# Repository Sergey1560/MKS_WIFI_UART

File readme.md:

# Модуль для подключения к UART плат Robin Nano

Данный модуль предназначен для использования с платами MKS Robin Nano. Вставляется вместо MKS WIFI модуля и позволяет подключиться по UART. На модуле установлен изолятор ISO 7712 и USB-UART преобразователь FT230. На разъем J3 выведены сигналы USB, на разъем J4 выведены сигналы UART.

Проект сделан в KiCad.

## Схема платы

## Архив с gerber файлами

[mks_wifi.zip](./gerber/mks_wifi.zip)

## Список компонентов

Список компонентов - [mks_wifi_bom.ods](./bom/mks_wifi_bom.ods)

| N  | Кол-во | Номинал | Размер | Link
| -----------| ---------- |---------|------- |----- |
| C1, C2     | 2          | 47pF    | 0805   | [LCSC](https://lcsc.com/product-detail/Multilayer-Ceramic-Capacitors-MLCC-SMD-SMT_YAGEO-CC0805JRNPO9BN470_C107118.html) [TERRA](https://spb.terraelectronica.ru/product/600072) |
| C3, C5     | 2          | 0.1uF   | 0805   | [LCSC](https://lcsc.com/product-detail/Multilayer-Ceramic-Capacitors-MLCC-SMD-SMT_YAGEO-CC0805KRX7R9BB104_C49678.html) [TERRA](https://spb.terraelectronica.ru/product/251110) |
| C4         | 1          | 4.7uF   | 0805   | [LCSC](https://lcsc.com/product-detail/Multilayer-Ceramic-Capacitors-MLCC-SMD-SMT_Murata-Electronics-GRM21BR61C475KA88L_C97915.html) [TERRA](https://spb.terraelectronica.ru/product/234492) |
| C6         | 1          | 0.01uF   | 0805   | [LCSC](https://lcsc.com/product-detail/Multilayer-Ceramic-Capacitors-MLCC-SMD-SMT_YAGEO-CC0805KRX7R9BB103_C83170.html) [TERRA](https://spb.terraelectronica.ru/product/1350309) |
| C7, C8     | 2          | 1uF   | 0805   | [LCSC](https://lcsc.com/product-detail/Multilayer-Ceramic-Capacitors-MLCC-SMD-SMT_Murata-Electronics-GCM21BR71H105KA03L_C126592.html) [TERRA](https://spb.terraelectronica.ru/product/884481) |
| J1, J2     | 2          | 1uF   | Conn_01x08 | [LCSC](https://lcsc.com/product-detail/Pin-Header-Female-Header_Ckmtw-Shenzhen-Cankemeng-Headers-Pins-1-8P-2-54mm-Straight-line_C124381.html) |
| J3, J4     | 2          | JST XH2.54 |  .  |
| R1, R2     | 2          | 27 Ом   | 0805   | [LCSC](https://lcsc.com/product-detail/Chip-Resistor-Surface-Mount_UNI-ROYAL-Uniroyal-Elec-0805W8F270JT5E_C17594.html) [TERRA](https://spb.terraelectronica.ru/product/871706) |
| U1         | 1          | FT230XS | SSOP-16 3.9x4.9mm P0.635mm | [LCSC](https://lcsc.com/product-detail/USB-ICs_FTDI-FT230XS-R_C69082.html) [TERRA](https://spb.terraelectronica.ru/product/1339655) |
| U2         | 1          | ISO7721 | SOIC-8 3.9x4.9mm P1.27mm | [LCSC](https://lcsc.com/product-detail/Digital-Isolators_Texas-Instruments-Texas-Instruments-ISO7721DR_C366164.html) [TERRA](https://spb.terraelectronica.ru/product/2301597) |

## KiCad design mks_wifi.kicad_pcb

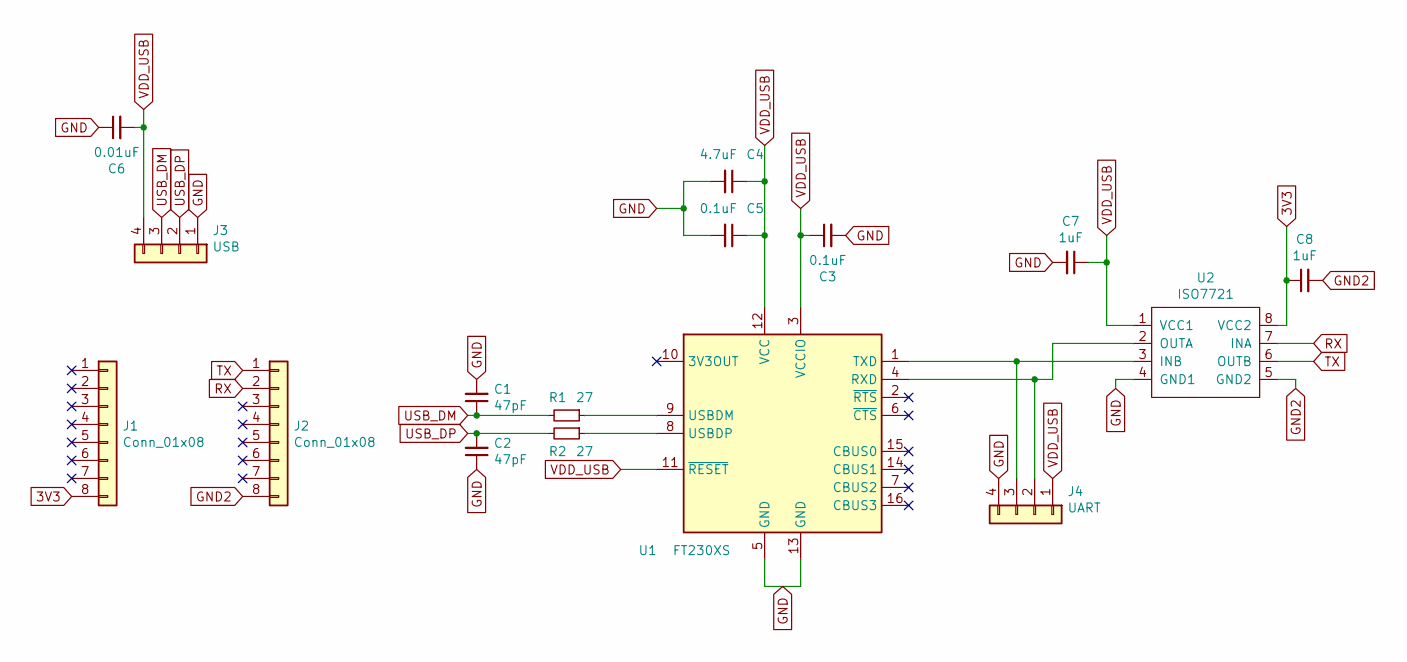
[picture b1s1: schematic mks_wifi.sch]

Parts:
C1, C2: 47pF; C_0805_2012Metric
C3, C5: 0.1uF; C_0805_2012Metric
C4: 4.7uF; C_0805_2012Metric
C6: 0.01uF; C_0805_2012Metric
C7, C8: 1uF; C_0805_2012Metric
J1, J2: Conn_01x08; PinHeader_1x08_P2.54mm_Vertical
J3: USB; JST_XH_B4B-XH-A_1x04_P2.50mm_Vertical
J4: UART; JST_XH_B4B-XH-A_1x04_P2.50mm_Vertical
R1, R2: 27; R_0805_2012Metric
U1: FT230XS; SSOP-16_3.9x4.9mm_P0.635mm
U2: ISO7721; SOIC-8_3.9x4.9mm_P1.27mm

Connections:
3V3: C8.1, J1.8, U2.8 (VCC2)
GND: C1.2, C2.1, C3.2, C4.2, C5.2, C6.1, C7.2, J3.1, J4.4, U1.5 (GND), U1.13 (GND), U2.4 (GND1)
GND2: C8.2, J2.8, U2.5 (GND2)
unnamed: J4.2, U1.4 (RXD), U2.2 (OUTA)
unnamed: J4.3, U1.1 (TXD), U2.3 (INB)
unnamed: R1.1, U1.9 (USBDM)
unnamed: R2.1, U1.8 (USBDP)
RX: J2.2, U2.7 (INA)
TX: J2.1, U2.6 (OUTB)
USB_DM: C1.1, J3.3, R1.2
USB_DP: C2.2, J3.2, R2.2
VDD_USB: C3.1, C4.1, C5.1, C6.2, C7.1, J3.4, J4.1, U1.3 (VCCIO), U1.11 (~RESET), U1.12 (VCC), U2.1 (VCC1)

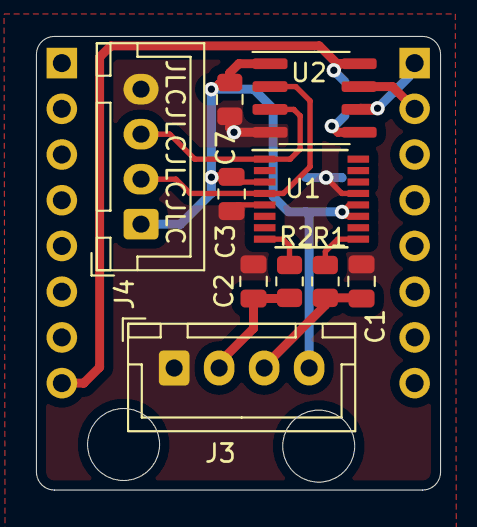
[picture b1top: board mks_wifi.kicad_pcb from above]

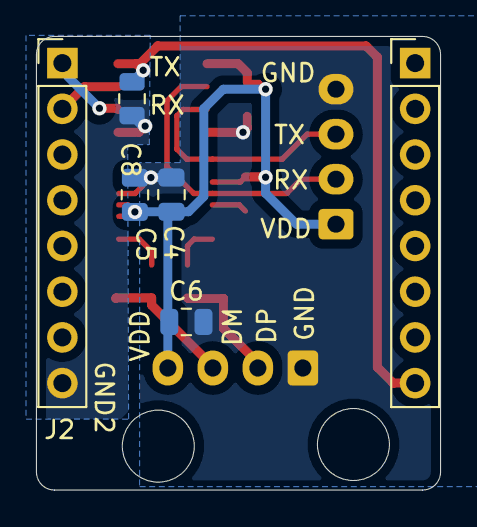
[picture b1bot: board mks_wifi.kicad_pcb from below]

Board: 2 copper layers, 22.5 x 25.2 mm, 16 parts (6 on the bottom side), 12 nets.

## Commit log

2021-02-09 Initial
2021-04-28 v1, проверенный вариант
2021-04-28 Readme, bom list
2021-04-28 readme
